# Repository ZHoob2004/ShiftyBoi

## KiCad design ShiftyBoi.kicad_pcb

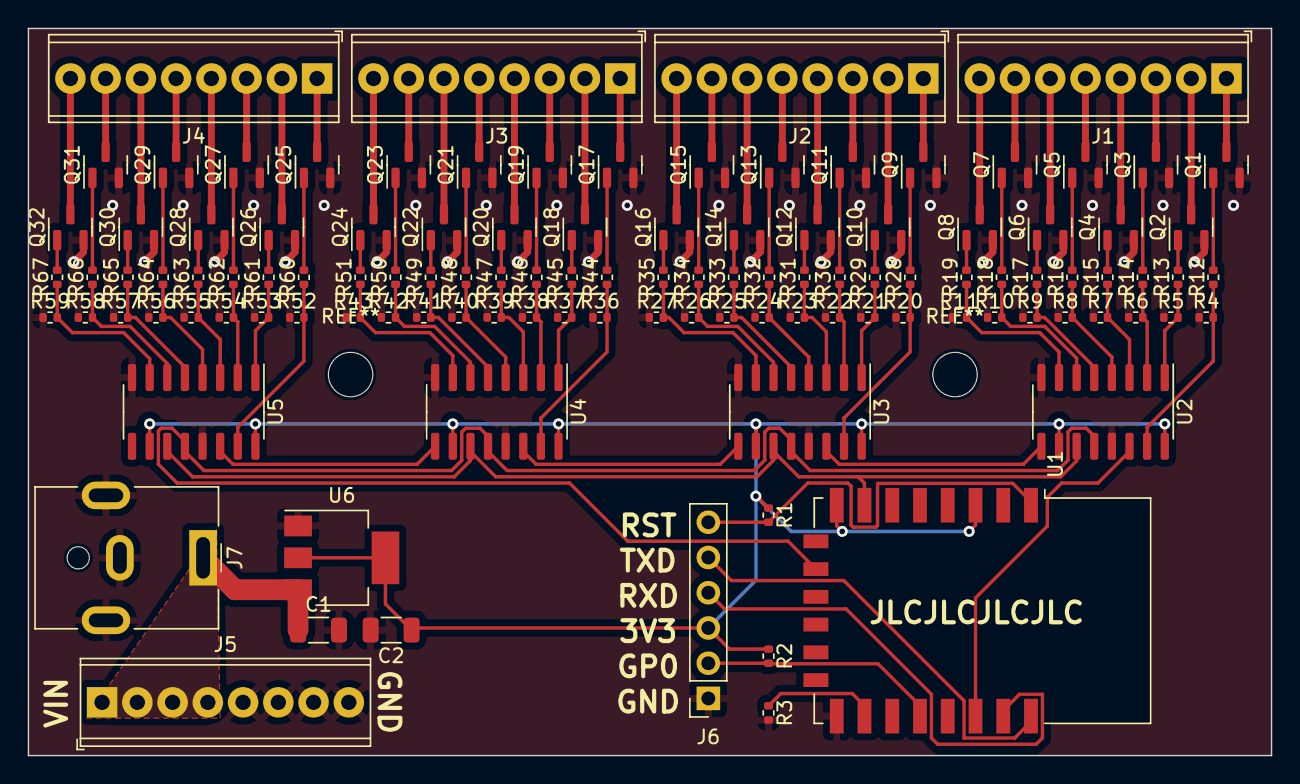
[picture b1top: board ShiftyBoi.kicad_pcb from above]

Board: 2 copper layers, 89.6 x 52.4 mm, 114 parts (0 on the bottom side), 110 nets.

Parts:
C1: 10uf; C_1206_3216Metric
C2: 100uf; C_1206_3216Metric
J1, J2, J3, J4, J5: Screw_Terminal_01x08; TerminalBlock_Phoenix_MPT-0,5-8-2.54_1x08_P2.54mm_Horizontal
J6: PROG; PinSocket_1x06_P2.54mm_Vertical
J7: Barrel_Jack_MountingPin; BarrelJack_CUI_PJ-063AH_Horizontal
Q1, Q2, Q3, Q4, Q5, Q6, Q7, Q8, Q9, Q10, Q11, Q12, Q13, Q14, Q15, Q16, Q17, Q18, Q19, Q20, Q21, Q22, Q23, Q24, Q25, Q26, Q27, Q28, Q29, Q30, Q31, Q32: AO3400A; SOT-23
R1: 4.7k; R_0402_1005Metric
R2, R3, R4, R5, R6, R7, R8, R9, R10, R11, R20, R21, R22, R23, R24, R25, R26, R27, R36, R37, R38, R39, R40, R41, R42, R43, R52, R53, R54, R55, R56, R57, R58, R59: 10k; R_0402_1005Metric
R12, R13, R14, R15, R16, R17, R18, R19, R28, R29, R30, R31, R32, R33, R34, R35, R44, R45, R46, R47, R48, R49, R50, R51, R60, R61, R62, R63, R64, R65, R66, R67: 1k; R_0402_1005Metric
U1: ESP-12F; ESP-12E
U2, U3, U4, U5: 74HC595; SOIC-16_3.9x9.9mm_P1.27mm
U6: AMS1117-3.3; SOT-223-3_TabPin2

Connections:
+3V3: C2.1, J6.3, R1.1, R2.1, U1.3 (EN), U1.8 (VCC), U2.10 (~SRCLR), U2.16 (VCC), U3.10 (~SRCLR), U3.16 (VCC), U4.10 (~SRCLR), U4.16 (VCC), U5.10 (~SRCLR), U5.16 (VCC), U6.2 (VO)
+12V: C1.1, J5.1, J5.2, J5.3, J5.4, J7.1, U6.3 (VI)
/Driver1: R4.2, R12.1, U2.15 (QA)
/Driver2: R5.2, R13.1, U2.1 (QB)
/Driver3: R6.2, R14.1, U2.2 (QC)
/Driver4: R7.2, R15.1, U2.3 (QD)
/Driver5: R8.2, R16.1, U2.4 (QE)
/Driver6: R9.2, R17.1, U2.5 (QF)
/Driver7: R10.2, R18.1, U2.6 (QG)
/Driver8: R11.2, R19.1, U2.7 (QH)
/Driver9: R20.2, R28.1, U3.15 (QA)
/Driver10: R21.2, R29.1, U3.1 (QB)
/Driver11: R22.2, R30.1, U3.2 (QC)
/Driver12: R23.2, R31.1, U3.3 (QD)
/Driver13: R24.2, R32.1, U3.4 (QE)
/Driver14: R25.2, R33.1, U3.5 (QF)
/Driver15: R26.2, R34.1, U3.6 (QG)
/Driver16: R27.2, R35.1, U3.7 (QH)
/Driver17: R36.2, R44.1, U4.15 (QA)
/Driver18: R37.2, R45.1, U4.1 (QB)
/Driver19: R38.2, R46.1, U4.2 (QC)
/Driver20: R39.2, R47.1, U4.3 (QD)
/Driver21: R40.2, R48.1, U4.4 (QE)
/Driver22: R41.2, R49.1, U4.5 (QF)
/Driver23: R42.2, R50.1, U4.6 (QG)
/Driver24: R43.2, R51.1, U4.7 (QH)
/Driver25: R52.2, R60.1, U5.15 (QA)
/Driver26: R53.2, R61.1, U5.1 (QB)
/Driver27: R54.2, R62.1, U5.2 (QC)
/Driver28: R55.2, R63.1, U5.3 (QD)
/Driver29: R56.2, R64.1, U5.4 (QE)
/Driver30: R57.2, R65.1, U5.5 (QF)
/Driver31: R58.2, R66.1, U5.6 (QG)
/Driver32: R59.2, R67.1, U5.7 (QH)
/Drivers/OUT1: J1.1, Q1.3 (D)
/Drivers/OUT2: J1.2, Q2.3 (D)
/Drivers/OUT3: J1.3, Q3.3 (D)
/Drivers/OUT4: J1.4, Q4.3 (D)
/Drivers/OUT5: J1.5, Q5.3 (D)
/Drivers/OUT6: J1.6, Q6.3 (D)
/Drivers/OUT7: J1.7, Q7.3 (D)
/Drivers/OUT8: J1.8, Q8.3 (D)
/Drivers/OUT9: J2.1, Q9.3 (D)
/Drivers/OUT10: J2.2, Q10.3 (D)
/Drivers/OUT11: J2.3, Q11.3 (D)
/Drivers/OUT12: J2.4, Q12.3 (D)
/Drivers/OUT13: J2.5, Q13.3 (D)
/Drivers/OUT14: J2.6, Q14.3 (D)
/Drivers/OUT15: J2.7, Q15.3 (D)
/Drivers/OUT16: J2.8, Q16.3 (D)
/Drivers/OUT17: J3.1, Q17.3 (D)
/Drivers/OUT18: J3.2, Q18.3 (D)
/Drivers/OUT19: J3.3, Q19.3 (D)
/Drivers/OUT20: J3.4, Q20.3 (D)
/Drivers/OUT21: J3.5, Q21.3 (D)
/Drivers/OUT22: J3.6, Q22.3 (D)
/Drivers/OUT23: J3.7, Q23.3 (D)
/Drivers/OUT24: J3.8, Q24.3 (D)
/Drivers/OUT25: J4.1, Q25.3 (D)
/Drivers/OUT26: J4.2, Q26.3 (D)
/Drivers/OUT27: J4.3, Q27.3 (D)
/Drivers/OUT28: J4.4, Q28.3 (D)
/Drivers/OUT29: J4.5, Q29.3 (D)
/Drivers/OUT30: J4.6, Q30.3 (D)
/Drivers/OUT31: J4.7, Q31.3 (D)
/Drivers/OUT32: J4.8, Q32.3 (D)
/GPIO0: J6.2, R2.2, U1.18 (GPIO0)
/RCLK: U1.10 (MISO), U2.12 (RCLK), U3.12 (RCLK), U4.12 (RCLK), U5.12 (RCLK)
/RST: J6.6, R1.2, U1.1 (~RST)
/RXD: J6.4, U1.21 (GPIO3/RXD)
/SER: U1.20 (GPIO5), U2.14 (SER)
/SRCLK: U1.7 (GPIO13), U2.11 (SRCLK), U3.11 (SRCLK), U4.11 (SRCLK), U5.11 (SRCLK)
/TXD: J6.5, U1.22 (GPIO1/TXD)
GND: C1.2, C2.2, J5.5, J5.6, J5.7, J5.8, J6.1, J7.2, J7.MP (MountPin), Q1.2 (S), Q2.2 (S), Q3.2 (S), Q4.2 (S), Q5.2 (S), Q6.2 (S), Q7.2 (S), Q8.2 (S), Q9.2 (S), Q10.2 (S), Q11.2 (S), Q12.2 (S), Q13.2 (S), Q14.2 (S), Q15.2 (S), Q16.2 (S), Q17.2 (S), Q18.2 (S), Q19.2 (S), Q20.2 (S), Q21.2 (S), Q22.2 (S), Q23.2 (S), Q24.2 (S), Q25.2 (S), Q26.2 (S), Q27.2 (S), Q28.2 (S), Q29.2 (S), Q30.2 (S), Q31.2 (S), Q32.2 (S), R3.2, R4.1, R5.1, R6.1, R7.1, R8.1, R9.1, R10.1, R11.1, R20.1, R21.1, R22.1, R23.1, R24.1, R25.1, R26.1, R27.1, R36.1, R37.1, R38.1, R39.1, R40.1, R41.1, R42.1, R43.1, R52.1, R53.1, R54.1, R55.1, R56.1, R57.1, R58.1, R59.1, U1.15 (GND), U2.8 (GND), U2.13 (~OE), U3.8 (GND), U3.13 (~OE), U4.8 (GND), U4.13 (~OE), U5.8 (GND), U5.13 (~OE), U6.1 (GND)
unnamed: Q1.1 (G), R12.2
unnamed: Q2.1 (G), R13.2
unnamed: Q3.1 (G), R14.2
unnamed: Q4.1 (G), R15.2
unnamed: Q5.1 (G), R16.2
unnamed: Q6.1 (G), R17.2
unnamed: Q7.1 (G), R18.2
unnamed: Q8.1 (G), R19.2
unnamed: Q9.1 (G), R28.2
unnamed: Q10.1 (G), R29.2
unnamed: Q11.1 (G), R30.2
unnamed: Q12.1 (G), R31.2
unnamed: Q13.1 (G), R32.2
unnamed: Q14.1 (G), R33.2
unnamed: Q15.1 (G), R34.2
unnamed: Q16.1 (G), R35.2
unnamed: Q17.1 (G), R44.2
unnamed: Q18.1 (G), R45.2
unnamed: Q19.1 (G), R46.2
unnamed: Q20.1 (G), R47.2
unnamed: Q21.1 (G), R48.2
unnamed: Q22.1 (G), R49.2
unnamed: Q23.1 (G), R50.2
unnamed: Q24.1 (G), R51.2
unnamed: Q25.1 (G), R60.2
unnamed: Q26.1 (G), R61.2
unnamed: Q27.1 (G), R62.2
unnamed: Q28.1 (G), R63.2
unnamed: Q29.1 (G), R64.2
unnamed: Q30.1 (G), R65.2
unnamed: Q31.1 (G), R66.2
unnamed: Q32.1 (G), R67.2
unnamed: R3.1, U1.16 (GPIO15)
unnamed: U2.9 (QH'), U3.14 (SER)
unnamed: U3.9 (QH'), U4.14 (SER)
unnamed: U4.9 (QH'), U5.14 (SER)

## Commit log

2023-05-08 added kicad project
2023-05-09 initial pcb construction
2023-05-10 More pcb layout
2023-05-17 even more pcb layout
2023-05-17 Final PCB Layout
